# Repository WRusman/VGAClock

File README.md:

Re-use an old VGA monitor with an ESP32 WROOM (DEVKIT-V1) 

Be sure to compile with the esp32 version 2 (2.0.17) core

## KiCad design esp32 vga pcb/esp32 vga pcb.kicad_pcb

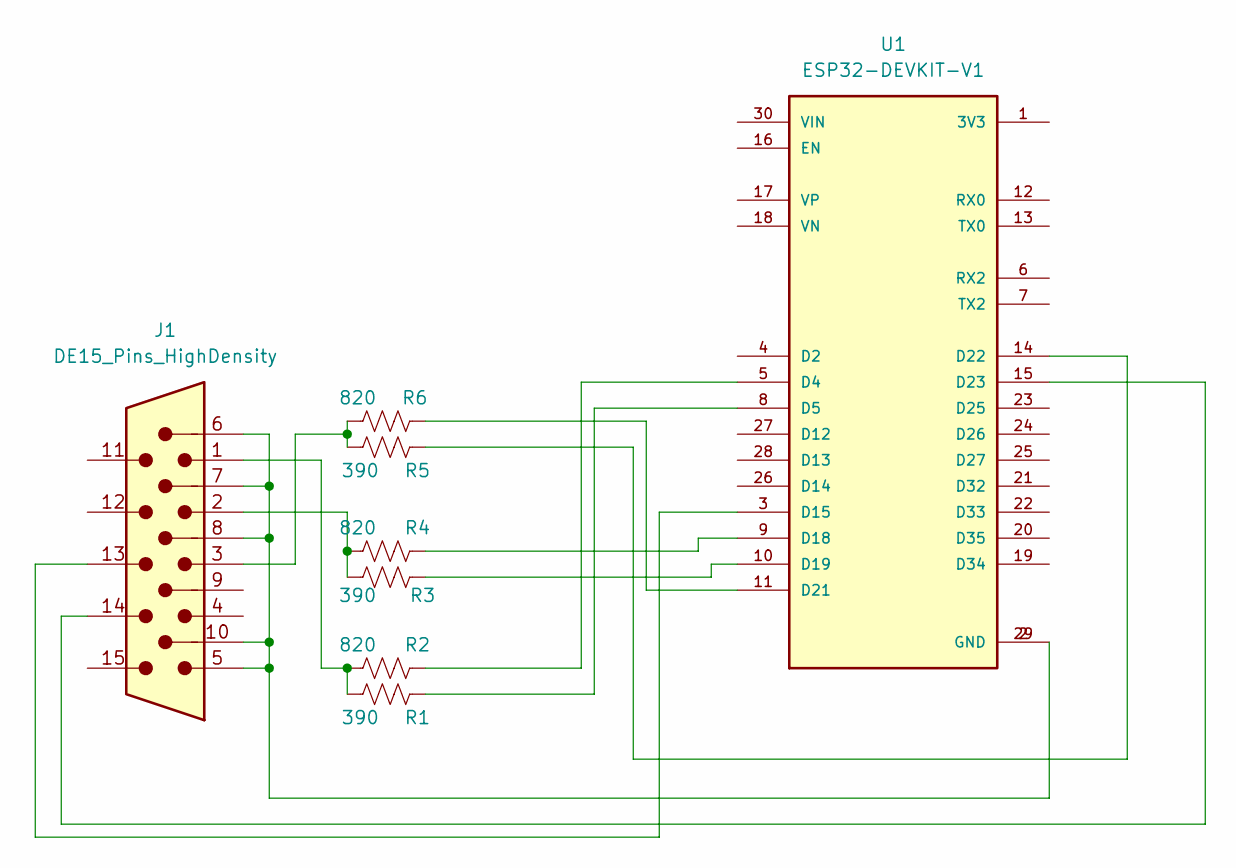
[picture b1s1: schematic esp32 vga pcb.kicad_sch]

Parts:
J1: DE15_Pins_HighDensity; DSUB-15-HD_Pins_Horizontal_P2.29x2.54mm_EdgePinOffset8.35mm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
R1, R3, R5: 390; R_Axial_DIN0207_L6.3mm_D2.5mm_P10.16mm_Horizontal
R2, R4, R6: 820; R_Axial_DIN0207_L6.3mm_D2.5mm_P10.16mm_Horizontal
U1: ESP32-DEVKIT-V1; MODULE_ESP32_DEVKIT_V1; PARTREV N/A

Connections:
unnamed: J1.1, R1.1, R2.1
unnamed: J1.2, R3.1, R4.1
unnamed: J1.3, R5.1, R6.1
unnamed: J1.5, J1.6, J1.7, J1.8, J1.10, U1.2 (GND), U1.29 (GND)
unnamed: R2.2, U1.5 (D4)
unnamed: R1.2, U1.8 (D5)
unnamed: J1.13, U1.3 (D15)
unnamed: R4.2, U1.9 (D18)
unnamed: R3.2, U1.10 (D19)
unnamed: R6.2, U1.11 (D21)
unnamed: R5.2, U1.14 (D22)
unnamed: J1.14, U1.15 (D23)

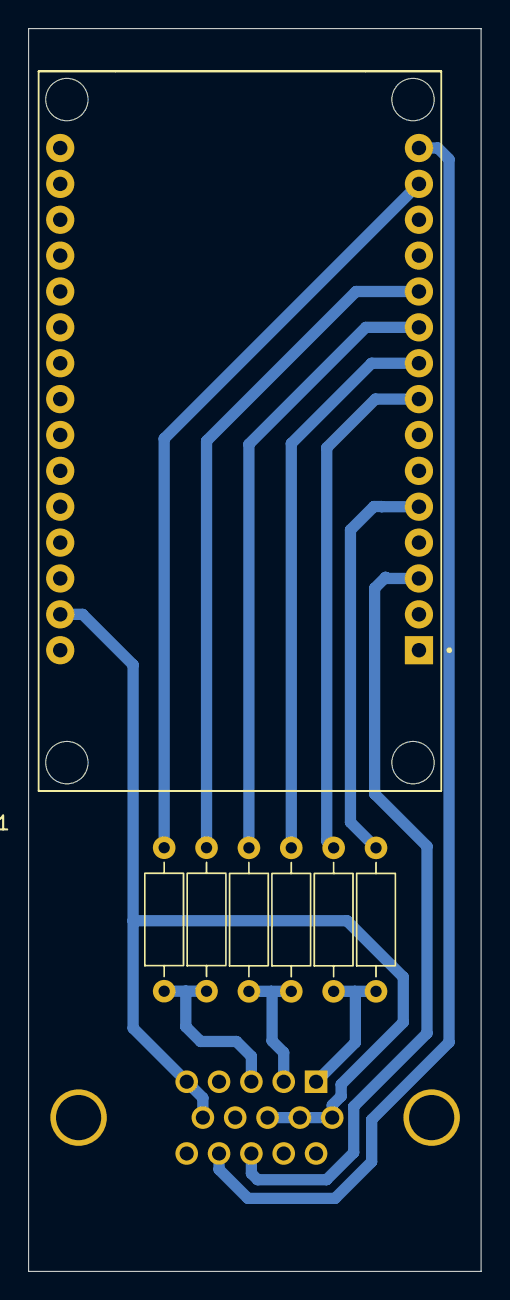
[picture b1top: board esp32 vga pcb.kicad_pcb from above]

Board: 2 copper layers, 32.0 x 88.0 mm, 8 parts (1 on the bottom side), 12 nets.
